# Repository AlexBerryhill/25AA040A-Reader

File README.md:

# 25AA040A Reader
 A PCB that will read a 25AA040A EEPROM using an esp32 devkitC-1

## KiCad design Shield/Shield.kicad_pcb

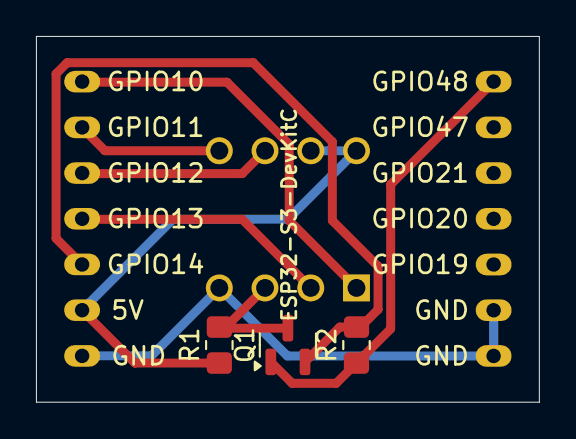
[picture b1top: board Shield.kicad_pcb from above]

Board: 2 copper layers, 27.9 x 20.3 mm, 5 parts (1 on the bottom side), 9 nets.

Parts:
Q1: BSS138; SOT-23
R1, R2: R_US; R_0805_2012Metric_Pad1.20x1.40mm_HandSolder
U1: 25aa040a-i/p; PDIP8_300MC_MCH
U2: ESP32-S3-DevKitC

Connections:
+3V3: Q1.1 (G), R2.1, U2.29 (GPIO48)
+5V: R1.1, U1.7 (HOLD*), U1.8 (VCC), U2.21 (5V)
CS: U1.1 (CS*), U2.16 (GPIO10/ADC1_CH9)
GND: U1.4 (VSS), U2.22 (GND), U2.23 (GND), U2.24 (GND)
HVWP: Q1.3 (D), R1.2, U1.3 (WP*)
LVWP: Q1.2 (S), R2.2, U2.20 (GPIO14/ADC2_CH3)
MISO: U1.2 (SO), U2.19 (GPIO13/ADC2_CH2)
MOSI: U1.5 (SI), U2.17 (GPIO11/ADC2_CH0)
SCK: U1.6 (SCK), U2.18 (GPIO12/ADC2_CH1)

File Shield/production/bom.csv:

Designator,Footprint,Quantity,Value,LCSC Part #
U1,PDIP8_300MC_MCH,1,25aa040a-i/p,
U2,ESP32-S3-DevKitC,1,ESP32-S3-DevKitC,

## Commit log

2025-03-12 update production file
2025-03-26 Added devkitc code
2025-04-02 change address calling
2025-04-02 Added level shifter
